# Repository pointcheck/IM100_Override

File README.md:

# Paslode IM100C vendor lock-in override 

This repository contains PCB schematics and firmware for the device to override vendor lock-in for Paslode IM100C gas actuated nail hammer.

## Disclaimer

This small one weekend project is provided here solely for educational purpose to demostrate how weak and futile vendor lock-ins can be at places it should not be present in essence and how easy it is to overcome it. Note, that overcomming (removing) vendor lock-in is illigal in many countries even for personal use, one can be sued or fined for doing so. You've been warned!

## Details

Paslode IM100C is a gas actuated nailing system (stapling hammer) that uses natural gas (propane/butane mixture) to fuel hammer working by internal combustion principle, i.e. by injecting a dose of fuel into combustion chamber and igniting mixture with electrical spark, like it goes in any gasoline engine.

Paslode IM100C is very useful and handy device which can be used both by DIY and professional carpenters or wood workers. The problem is that fuel cartridges (cylindrical tanks with gas mixture) are equipped with RFID tags (NFC 13MHz standard) that store a decreasing counter of nails you can fire, usually not more than 1250 shots, thus limiting users and enforcing them to purchase "genuine" fuel cartridges. These cartridges come at a cost of course, somewhat about 100+ EURO each. Many users discovered that it is possible to refill cartridges with a gas purchased from nearby hardware store, but you still will be limited to a number of shots because of the above vendor lock-in mechanism.

One can disassemble IM100C hammer and see that vendor made significant effort to make lock-in hard to override. There are two MCU powered devices (PCBs) inside. One is controlling fuel injection and ignition mechanism, and the other for gas valve. It is the last one that prevents fuel to come from cartridge to the chamber if not proper (or outdated) RFID tag found. These two controllers communicate to each other using digital (I2C) interface. There are also two digital buttons that produce PWM signals on their outputs. One button is tied to shutter mechanism and signals when it is time to refill chamber with new dose of fuel, the other one is a fire trigger user pulls to make a nail shot. Both controllers (PCBs) are immersed into some kind of compound making reverse-engineering not easy to perform.

Yet, there is a way to work-around this vendor lock-in. A simple analysis shown that sparks are being produced even if hammer is missing proper fuel cartridge. So, if one can open gas valve in-time (and for a proper time period) to let fuel in into the chamber, the hammer will work. Thus, to overcome vendor lock-in a simple MCU device can be used to control gas valve directly bypassing vendor's mechanism. This MCU device should be connected directly to shutter button and to the valve, making valve to open for a 15ms when shutter button is pressed. It is not necessary to disconnect shutter button and valve from original electronics, one can keep them running in parallel.

It was discovered, that gas injection time varies depending on ambient temperature, i.e. injection time increases when temperature goes down. The maximum injection time is ~40ms at temperatures -20C. Thus an NTC thermistor was introduced into override PCB board schematics and simple aproximation table is used in software.

## Safty instructions

If you decide to implement this vendor lock-in override device, please make sure you disassemble and assemble back your hammer with a) bettery and fuel cartridge removed, b) with gas chamber emptied priorly. Not doing so may lead to unexpected gas ignition and shot causing serious injury! Also, test device with hammer fully assembled and all the nuts are tightened! Please, be precautious!

## Images

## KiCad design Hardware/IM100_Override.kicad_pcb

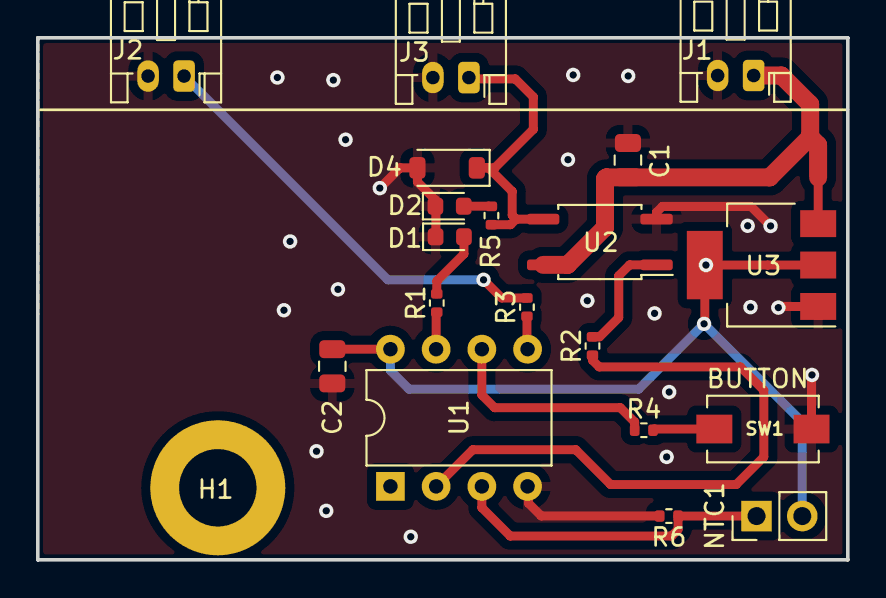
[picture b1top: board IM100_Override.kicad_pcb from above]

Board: 2 copper layers, 45.0 x 29.0 mm, 20 parts (0 on the bottom side), 14 nets.

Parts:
C1, C2: 22uF/25V; C_0805_2012Metric
D1: FYLS-0603PGC; LED_0603_1608Metric
D2: FYLS-0603URC; LED_0603_1608Metric
D4: 1N4148W; D_SOD-123
H1: MountingHole; MountingHole_4.3mm_M4_DIN965_Pad
J1, J2, J3: S2B-PH-K-S (LF)(SN); JST_PH_S2B-PH-K_1x02_P2.00mm_Horizontal
NTC1: 4.7K NTC; PinHeader_1x02_P2.54mm_Vertical
R1: 330R/1%; R_0402_1005Metric
R2, R5: 1K/1%; R_0402_1005Metric
R3, R4: 110R/1%; R_0402_1005Metric
R6: 10K/1%; R_0402_1005Metric
SW1: SW_Push; SW_SPST_EVQPE1
U1: ATtiny13-20P; DIP-8_W7.62mm
U2: TLP3123; SO-4_4.4x3.9mm_P2.54mm
U3: AMS1117-3.3; SOT-223-3_TabPin2

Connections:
+3V3: C2.1, NTC1.2, U1.8 (VCC), U3.2 (VO)
+BATT: C1.1, J1.1, U2.4, U3.3 (VI)
BUTTON: R4.2, SW1.1
GND: C1.2, C2.2, D1.1 (K), D2.1 (K), D4.2 (A), J1.2, J2.2, J3.2, R6.2, SW1.2, U1.4 (GND), U2.2, U3.1 (GND)
unnamed: D1.2 (A), R1.2
unnamed: D2.2 (A), R5.2
unnamed: R2.2, U2.1
unnamed: R3.1, U1.5 (PB0)
unnamed: R4.1, U1.6 (PB1)
unnamed: R1.1, U1.7 (PB2)
unnamed: R2.1, U1.2 (PB3)
unnamed: NTC1.1, R6.1, U1.3 (PB4)
SHUTTER: J2.1, R3.2
VALVE: D4.1 (K), J3.1, R5.1, U2.3

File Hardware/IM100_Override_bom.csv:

"Source:";"/P/PROJECTS/IM100_Override/Hardware/IM100_Override.kicad_sch"
"Date:";"Sat 28 Oct 16:27:46 2023"
"Tool:";"Eeschema 7.0.2"
"Generator:";"/usr/local/share/kicad/plugins/bom_csv_fabmicro.py"
"Component Count:";"20"
"Ref";"Qnty";"Value";"Cmp name";"Footprint";"Description";"Vendor";"Mfr. Part Number"
"C1, C2, ";"2";"22uF/25V";"CapacitorUnpolarized";"Capacitor_SMD:C_0805_2012Metric";"";"";"CL21A226MAQNNNE"
"D1, ";"1";"FYLS-0603PGC";"LED";"LED_SMD:LED_0603_1608Metric";"Light emitting diode";"";"FYLS-0603PGC"
"D2, ";"1";"FYLS-0603URC";"LED";"LED_SMD:LED_0603_1608Metric";"Light emitting diode";"";"FYLS-0603PGC"
"D4, ";"1";"1N4148W";"1N4148W";"Diode_SMD:D_SOD-123";"75V 0.15A Fast Switching Diode, SOD-123";"";"1N4148W"
"H1, ";"1";"MountingHole";"MountingHole";"MountingHole:MountingHole_4.3mm_M4_DIN965_Pad";"Mounting Hole without connection";"";""
"J1, J2, J3, ";"3";"S2B-PH-K-S (LF)(SN)";"CONN_2Pins";"Connector_JST:JST_PH_S2B-PH-K_1x02_P2.00mm_Horizontal";"Connector, 2 Pins";"";"S2B-PH-K-S (LF)(SN)"
"NTC1, ";"1";"4.7K NTC";"PT100";"Connector_PinHeader_2.54mm:PinHeader_1x02_P2.54mm_Vertical";"PT100 platinum temperature sensor (RTD)";"";""
"R1, ";"1";"330R/1%";"Resistor";"Resistor_SMD:R_0402_1005Metric";"";"";"RC0402FR-07330RL"
"R2, R5, ";"2";"1K/1%";"Resistor";"Resistor_SMD:R_0402_1005Metric";"";"";"RC0402FR-071KL"
"R3, R4, ";"2";"110R/1%";"Resistor";"Resistor_SMD:R_0402_1005Metric";"";"";"RC0402FR-07110RL"
"R6, ";"1";"10K/1%";"Resistor";"Resistor_SMD:R_0402_1005Metric";"";"";"RC0402FR-0710KL"
"SW1, ";"1";"SW_Push";"SW_Push";"Button_Switch_SMD:SW_SPST_EVQPE1";"Push button switch, generic, two pins";"";"DTSM-32"
"U1, ";"1";"ATtiny13-20P";"ATtiny13-20P";"Package_DIP:DIP-8_W7.62mm";"20MHz, 1kB Flash, 64B SRAM, 64B EEPROM, debugWIRE, DIP-8";"";""
"U2, ";"1";"TLP3123";"TLP3123";"Package_SO:SO-4_4.4x3.9mm_P2.54mm";"Solid State Relay (Photo MOSFET) 40V, 1A, 0.1Ohm, SO-4";"";""
"U3, ";"1";"AMS1117-3.3";"AMS1117-3.3";"Package_TO_SOT_SMD:SOT-223-3_TabPin2";"1A Low Dropout regulator, positive, 3.3V fixed output, SOT-223";"";""

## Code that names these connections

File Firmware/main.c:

/*
 * Firmware for ATTINY13A MCU to control gas valve
 * in Paslode IM100C vendor lock-in override device.
 *
 * Copyright (c) 2023 Ruslan Zalata.
 *
 */

#include <stdlib.h>
#include <util/delay.h>
#include <avr/io.h>
#include <avr/interrupt.h>
#include <avr/wdt.h>

#define GAS_OFF_TIME_MS	500U
#define	VREF		3300UL	// Vref = Vcc = 3.3V

unsigned long sensor_mv = 0;
unsigned int pulse_ms = 14;

// ADC at -30C = 195mV
// ADC at -20C = 593mV 
// ADC at -10C = 920mV
// ADC at   0C = 2153mV
// ADC at +20C = 2244mV
// ADC at +30C = 2398mv

struct _temp_to_pulse {
	unsigned long adc_mv;
	unsigned int pulse_ms;
} temp_to_pulse[] = {
	{0, 42}, // at -60C
	{195, 42}, // at -30C
	{593, 36}, // at -20C
	{920, 20}, // at -10C
	{2153, 18}, // at 0C
	{2244, 14}, // at +20C
	{2398, 10}, // at +30C
	{3300, 10}, // sentinel
};

unsigned int calc_pulse(unsigned long adc_mv) {
	int i;
	unsigned int cur_pulse_ms = 0;

	if(adc_mv < 5)
		return 0; // Something is wrong with NTC sensor

	for(i = 0; i < sizeof(temp_to_pulse) / sizeof(temp_to_pulse[0]); i++)
		if(adc_mv >= temp_to_pulse[i].adc_mv)
			cur_pulse_ms = temp_to_pulse[i].pulse_ms;

	return cur_pulse_ms;
}

int main(void)
{
	cli();

	DDRB |= (1<<DDB2); // Output: Heartbeat LED
	PORTB &= ~(1<<PB2); // Turn OFF LED

	DDRB |= (1<<DDB3); // Output: Gas valve
	PORTB &= ~(1<<PB3); // Close Gass valve (active high)

	DDRB &= ~(1<<DDB0); // Input: Shutter trigger 
	PORTB |= (1<<PB0); // Enable pull-up for Shutter trigger

	DDRB &= ~(1<<DDB1); // Input: User button 
	PORTB |= (1<<PB1); // Enable pull-up for User button

	// PB4 (ADC2) pin is input
	DDRB &= ~(1<<DDB4); // Input: ADC2 
	PORTB &= ~(1<<PB4); // No pull-up for ADC2 
	// Set the ADC mux to ADC2, enable left adjust, Vref = Vcc
	ADMUX = (1 << MUX1) | (1 << ADLAR);
	// Set the prescaler to clock/128, enable ADC, no IRQ
	ADCSRA = (1 << ADPS1) | (1 << ADPS0) | (1 << ADEN);

	PCMSK = _BV (PCINT0); // Enable external interrupts PCINT0
	MCUCR = _BV (ISC01); // The falling edge of PCINT0 generates IRQ 
	GIMSK = _BV (PCIE); // Pin Change Interrupt Enable

	// Enable Watchdog
        WDTCR |= (1<<WDCE) | (1<<WDE); // Allow WDT reconfig, then enable WDT
	WDTCR |= (1<<WDCE) | (1<<WDP3); // Allow WDT reconfig, then set timeout to 4s
	wdt_reset();

	sei();

	// Long blink on statup
	PORTB |= (1<<PB2);
	_delay_ms(2000);
	PORTB &= ~(1<<PB2);
	wdt_reset();

	while (1) {
		// Start new the conversion
		ADCSRA |= (1 << ADSC);

		// Toggle Heartbeat LED once a second 
		PORTB ^= (1<<PB2);

		// Ping watchdog 
		wdt_reset();

		_delay_ms(1000);

		// Wait ADC to complete conversion
		while (ADCSRA & (1 << ADSC));

		// Read, cals and average temperature
		sensor_mv = VREF * (unsigned long)ADCH / 256;

		// Critical section
		cli();
		pulse_ms = calc_pulse(sensor_mv);
		sei();
	}

	return 0;
}

ISR (PCINT0_vect)
{
	cli();

	if ((PINB & (1<<PB0)) == 0) {
		int i;
	
		PORTB |= (1<<PB2); // Heartbeat goes LED ON when gas valve open
		PORTB |= (1<<PB3); // Open gas valve	

		// Keep pulse as long as pulse_ms miliseconds
		for(i = 0; i < pulse_ms; i++)
			_delay_ms(1);

		PORTB &= ~(1<<PB3); // Close gas valve	
		_delay_ms(GAS_OFF_TIME_MS);
		PORTB &= ~(1<<PB2); // Heartbeat is LED goes OFF 

		GIFR |= 0b01100000;
	}

	sei();
}


ISR (WDT_vect) {
}

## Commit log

2023-10-12 Initial commit: only formware
2023-10-13 Initial commit: PCB schematics, board and gerber files
2023-10-13 Exclude fp-info-cache
2023-10-13 Add front/bottom mask to gerber files
2023-10-28 Add BoM file
2023-10-31 Output schematics file (PDF)
2023-11-01 Add temperature compensation through NTC sensor
2023-11-05 Add images with vendor lock-in override PCB installed on the device
2023-11-05 Update README: fix typos, add info about NTC sensor
2023-11-11 Add more images
2023-11-11 Add article in ODT and PDF format
2024-05-24 Add image of the installation kit
2024-05-24 Add installation instruction in Russian.
2024-05-25 Add PDF file with instruction in Russian.
2024-05-25 Installation guide: fix typos.
2024-05-25 Add laser cutter CAM files for box insert
2024-08-31 Makefile: Add linker stats output
2024-08-31 Enable Watchdog with 4s timeout
